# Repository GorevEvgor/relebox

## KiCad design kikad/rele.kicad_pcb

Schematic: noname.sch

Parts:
P1, P2, P3, P4, P5, P6, P7: CONNECTOR
Q1, Q2: BC548; TO92
R1, R2, R3, R4, R5, R6: R
U1, U2: TRD-5VDC-SC-CL

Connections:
+5: P6.1, R3.2, R4.1
-5: P7.1, Q1.3 (E), Q2.3 (E), R2.2, R6.2
L: P5.1, U1.5, U2.5
unnamed: P3.1, R5.1
unnamed: R4.2, U2.1
unnamed: P4.1, U2.3
unnamed: Q2.1 (C), U2.2
unnamed: Q1.1 (C), U1.1
unnamed: R3.1, U1.2
unnamed: P2.1, U1.3
unnamed: P1.1, R1.1
unnamed: Q1.2 (B), R1.2, R2.1
unnamed: Q2.2 (B), R5.2, R6.1

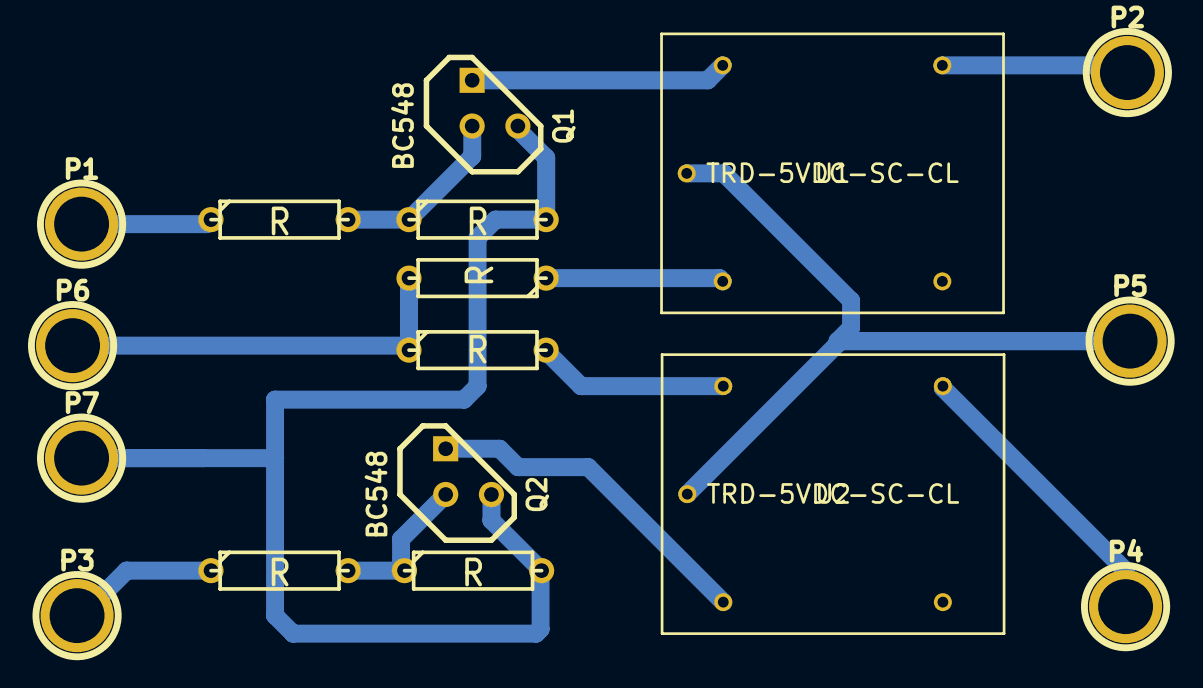
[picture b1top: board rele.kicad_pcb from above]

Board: 2 copper layers, 17 parts (0 on the bottom side), 13 nets.

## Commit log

2015-11-13 change to work with structure
2015-11-13 some tune and error check
2015-11-14 LED_pin for error count for VH_param structure
2015-11-14 kikad rele board
2015-11-14 fix temp[0] error
2015-11-15 add dialog whith time and state
2015-11-15 add debug dialog
2015-11-16 add logging functions
2017-11-25 переименова при отправке на гитхаб
